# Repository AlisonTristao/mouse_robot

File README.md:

# mouse_robot
Projeto da PCB de um robo para simular uma rede neural baseada no estudo do comportamento de roedores utilizando Arduino Mega

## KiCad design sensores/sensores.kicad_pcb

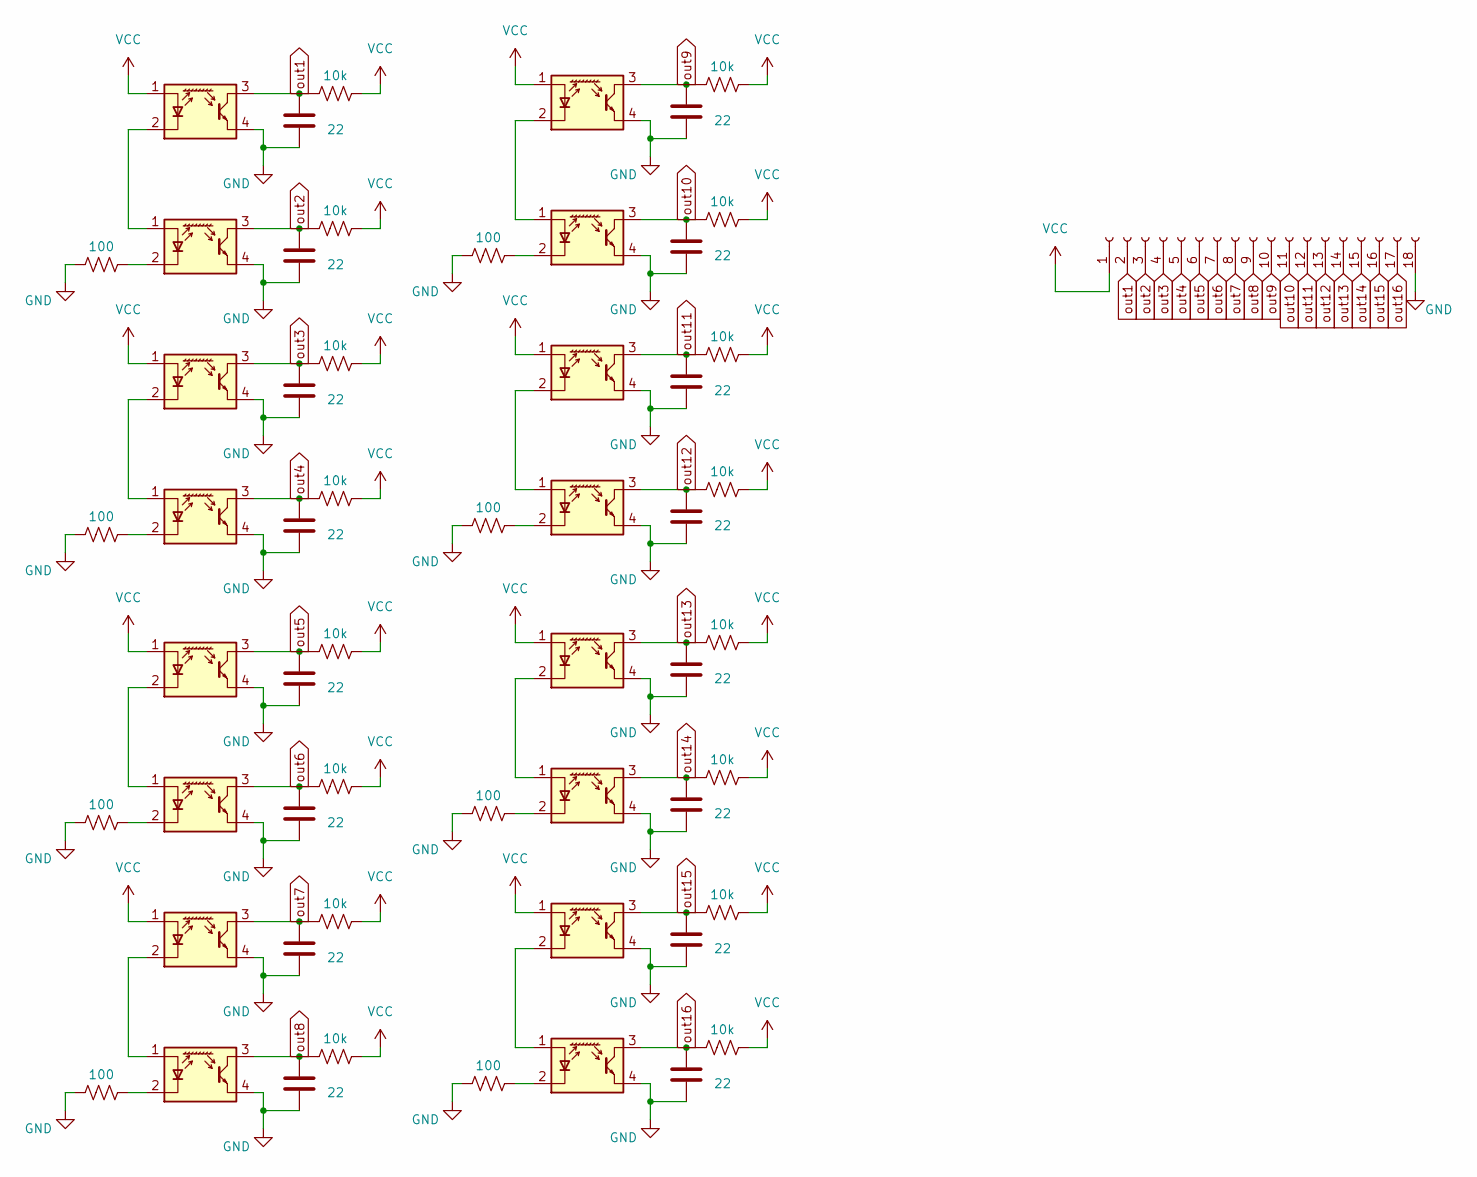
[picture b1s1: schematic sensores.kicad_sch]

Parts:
C1, C2, C3, C4, C5, C6, C7, C8, C9, C10, C11, C12, C13, C14, C15, C16: 22; C_1206_3216Metric
J1: Conn_01x18_Socket; PinSocket_1x18_P1.00mm_Vertical
R1, R4, R7, R8, R13, R14, R15, R16: 100; R_1206_3216Metric
R2, R3, R5, R6, R9, R10, R11, R12, R17, R18, R19, R20, R21, R22, R23, R24: 10k; R_1206_3216Metric
U1, U2, U3, U4, U5, U6, U7, U8, U9, U10, U11, U12, U13, U14, U15, U16: QRE1113GR; OnSemi_CASE100CY

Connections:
GND: C1.2, C2.2, C3.2, C4.2, C5.2, C6.2, C7.2, C8.2, C9.2, C10.2, C11.2, C12.2, C13.2, C14.2, C15.2, C16.2, J1.18, R1.1, R4.1, R7.1, R8.1, R13.1, R14.1, R15.1, R16.1, U1.4, U2.4, U3.4, U4.4, U5.4, U6.4, U7.4, U8.4, U9.4, U10.4, U11.4, U12.4, U13.4, U14.4, U15.4, U16.4
unnamed: U1.2 (K), U2.1 (A)
unnamed: R1.2, U2.2 (K)
unnamed: U3.2 (K), U4.1 (A)
unnamed: R4.2, U4.2 (K)
unnamed: U5.2 (K), U6.1 (A)
unnamed: R7.2, U6.2 (K)
unnamed: U7.2 (K), U8.1 (A)
unnamed: R8.2, U8.2 (K)
unnamed: U9.2 (K), U10.1 (A)
unnamed: R13.2, U10.2 (K)
unnamed: U11.2 (K), U12.1 (A)
unnamed: R14.2, U12.2 (K)
unnamed: U13.2 (K), U14.1 (A)
unnamed: R15.2, U14.2 (K)
unnamed: U15.2 (K), U16.1 (A)
unnamed: R16.2, U16.2 (K)
VCC: J1.1, R2.2, R3.2, R5.2, R6.2, R9.2, R10.2, R11.2, R12.2, R17.2, R18.2, R19.2, R20.2, R21.2, R22.2, R23.2, R24.2, U1.1 (A), U3.1 (A), U5.1 (A), U7.1 (A), U9.1 (A), U11.1 (A), U13.1 (A), U15.1 (A)
out1: C1.1, J1.2, R3.1, U1.3
out2: C2.1, J1.3, R2.1, U2.3
out3: C3.1, J1.4, R5.1, U3.3
out4: C4.1, J1.5, R6.1, U4.3
out5: C5.1, J1.6, R9.1, U5.3
out6: C6.1, J1.7, R10.1, U6.3
out7: C7.1, J1.8, R11.1, U7.3
out8: C8.1, J1.9, R12.1, U8.3
out9: C9.1, J1.10, R17.1, U9.3
out10: C10.1, J1.11, R18.1, U10.3
out11: C11.1, J1.12, R19.1, U11.3
out12: C12.1, J1.13, R20.1, U12.3
out13: C13.1, J1.14, R21.1, U13.3
out14: C14.1, J1.15, R22.1, U14.3
out15: C15.1, J1.16, R23.1, U15.3
out16: C16.1, J1.17, R24.1, U16.3

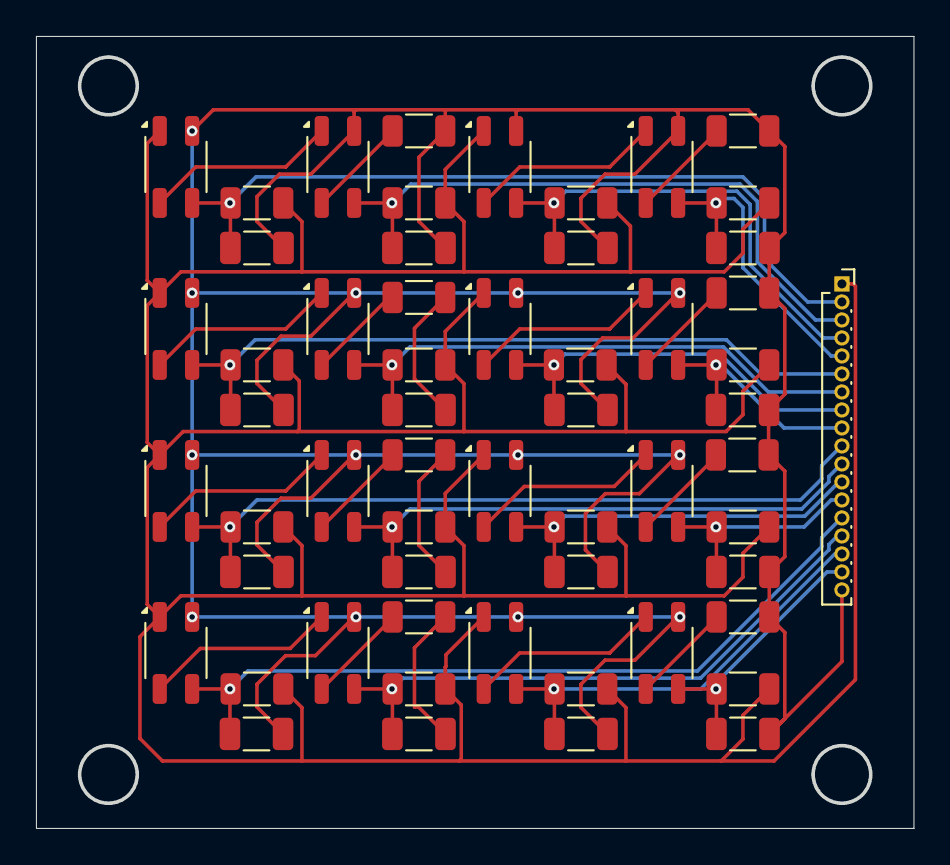
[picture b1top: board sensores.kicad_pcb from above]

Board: 2 copper layers, 48.6 x 43.9 mm, 57 parts (0 on the bottom side), 34 nets.

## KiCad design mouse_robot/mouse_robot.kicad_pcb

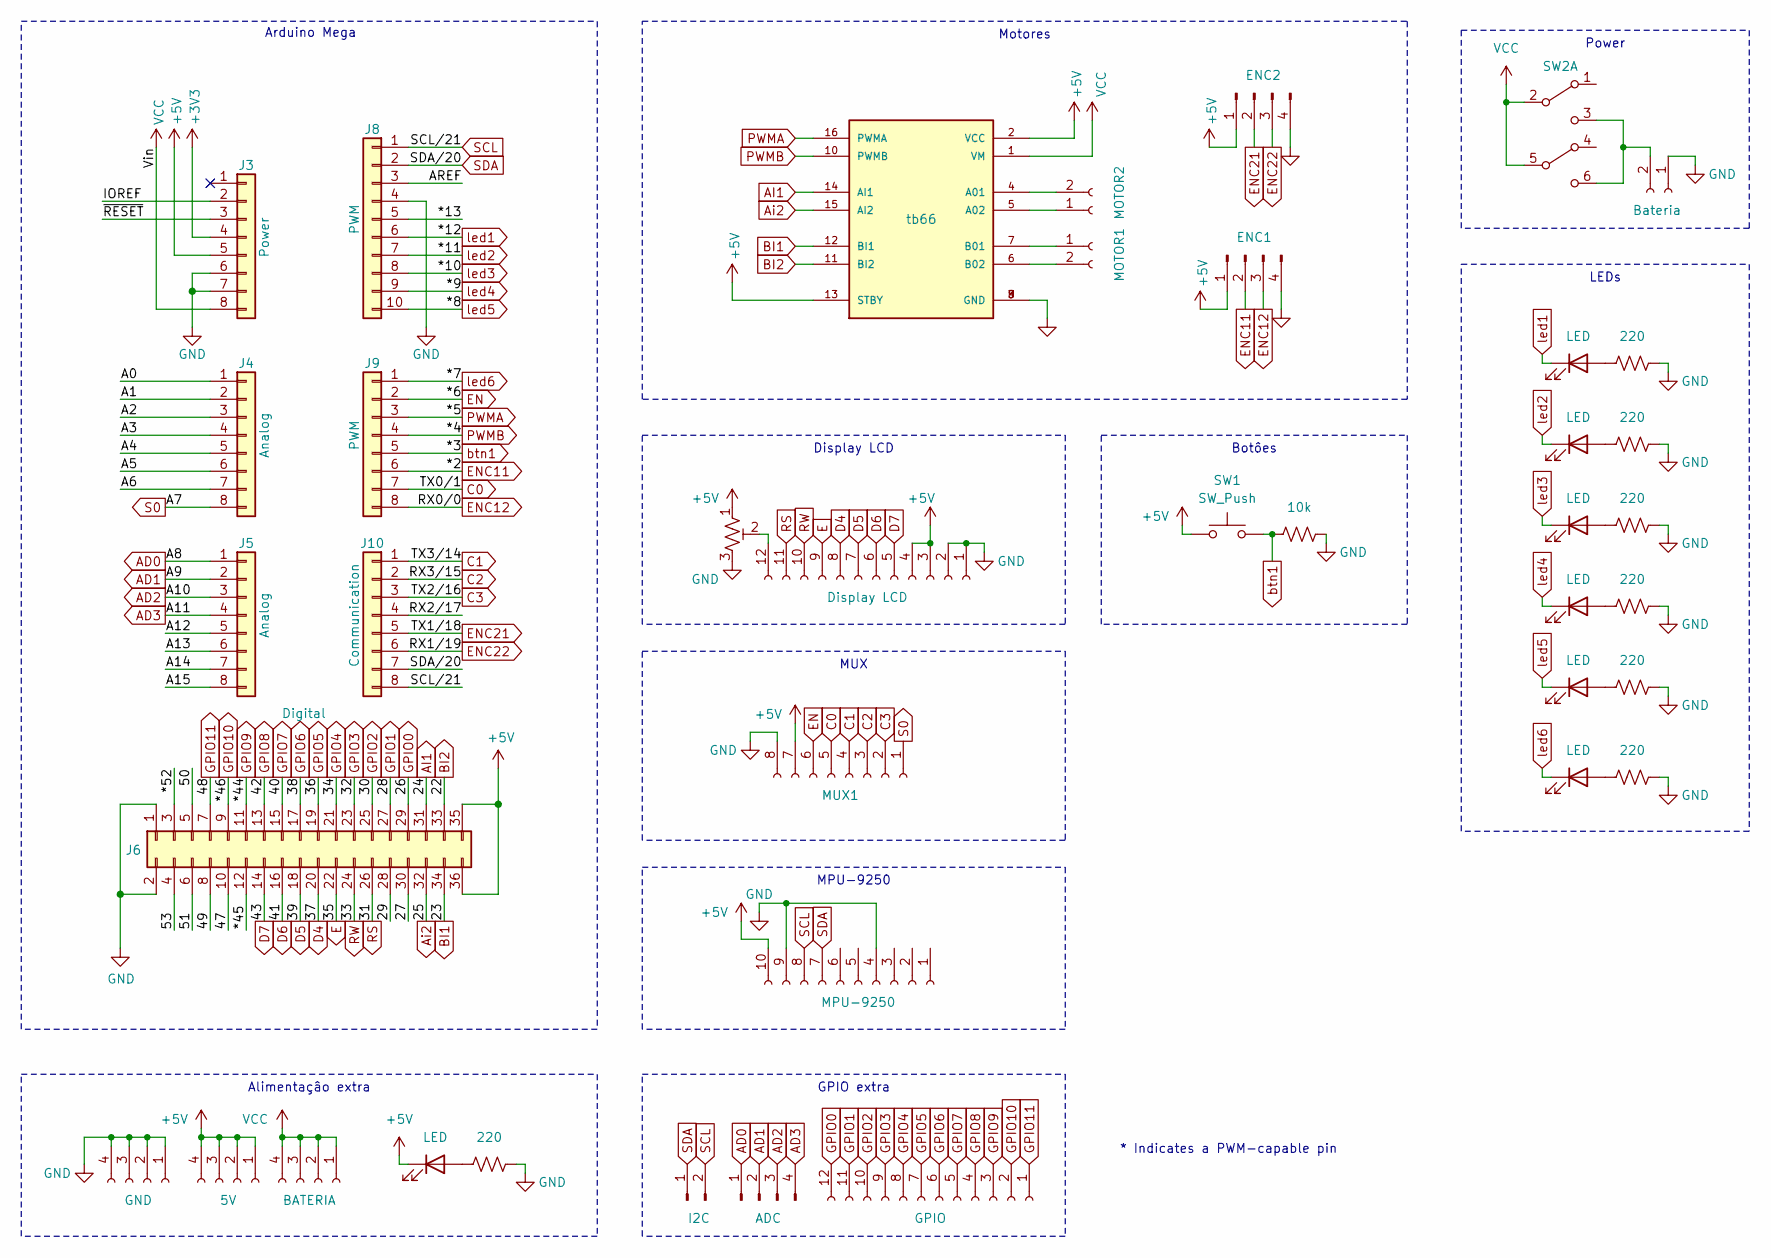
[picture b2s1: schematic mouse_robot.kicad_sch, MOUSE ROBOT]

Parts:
D1, D2, D3, D4, D5, D6, D7: LED; LED_1206_3216Metric
J1: GND; Molex_KK-254_AE-6410-04A_1x04_P2.54mm_Vertical
J2: 5V; Molex_KK-254_AE-6410-04A_1x04_P2.54mm_Vertical
J3: Power; PinSocket_1x08_P2.54mm_Vertical
J4, J5: Analog; PinSocket_1x08_P2.54mm_Vertical
J6: Digital; PinSocket_2x18_P2.54mm_Vertical
J7: BATERIA; Molex_KK-254_AE-6410-04A_1x04_P2.54mm_Vertical
J8: PWM; PinSocket_1x10_P2.54mm_Vertical
J9: PWM; PinSocket_1x08_P2.54mm_Vertical
J10: Communication; PinSocket_1x08_P2.54mm_Vertical
J11: I2C; Molex_KK-254_AE-6410-02A_1x02_P2.54mm_Vertical
J12: ADC; Molex_KK-254_AE-6410-04A_1x04_P2.54mm_Vertical
J13: MPU-9250; Molex_KK-254_AE-6410-10A_1x10_P2.54mm_Vertical
J14: Display LCD; Molex_KK-254_AE-6410-12A_1x12_P2.54mm_Vertical
J15: GPIO; Molex_KK-254_AE-6410-12A_1x12_P2.54mm_Vertical
MUX1: Conn_01x08_Socket; Molex_KK-254_AE-6410-08A_1x08_P2.54mm_Vertical
R1, R3, R4, R5, R6, R7, R8: 220; R_1206_3216Metric
R2: 10k; R_1206_3216Metric
RV1: Potenciometro; Potentiometer_Vishay_T73YP_Vertical
SW1: SW_Push; SW_PUSH_6mm_H4.3mm
SW2: SW_DPDT_x2
U1: tb66; MODULE_ROB-14450; PARTREV 11-13-17
con1: MOTOR2; Molex_KK-254_AE-6410-02A_1x02_P2.54mm_Vertical
con2: MOTOR1; Molex_KK-254_AE-6410-02A_1x02_P2.54mm_Vertical
con3: ENC1; Molex_KK-254_AE-6410-04A_1x04_P2.54mm_Vertical
con4: ENC2; Molex_KK-254_AE-6410-04A_1x04_P2.54mm_Vertical
con5: Bateria; Molex_KK-254_AE-6410-02A_1x02_P2.54mm_Vertical

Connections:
+3V3: J3.4
+5V: D1.1 (K), J2.1, J2.2, J2.3, J2.4, J3.5, J6.35, J6.36, J13.10, J14.3, J14.4, MUX1.7, RV1.1, SW1.1, U1.2 (VCC), U1.13 (STBY), con3.1, con4.1; also elsewhere on the board
/27: J6.30
/29: J6.28
/47: J6.10
/49: J6.8
/50: J6.5
/51: J6.6
/53: J6.4
/*13: J8.5
/*45: J6.12
/*52: J6.3
/A0: J4.1
/A1: J4.2
/A2: J4.3
/A3: J4.4
/A4: J4.5
/A5: J4.6
/A6: J4.7
/A12: J5.5
/A13: J5.6
/A14: J5.7
/A15: J5.8
/AREF: J8.3
/IOREF: J3.2
/RX2/17: J10.4
/~RESET: J3.3
AD0: J5.1, J12.1
AD1: J5.2, J12.2
AD2: J5.3, J12.3
AD3: J5.4, J12.4
AI1: J6.31, U1.14 (AI1)
Ai2: J6.32, U1.15 (AI2)
BI1: J6.34, U1.12 (BI1)
BI2: J6.33, U1.11 (BI2)
C0: J9.7, MUX1.5; also elsewhere on the board
C1: J10.1, MUX1.4; also elsewhere on the board
C2: J10.2, MUX1.3; also elsewhere on the board
C3: J10.3, MUX1.2; also elsewhere on the board
D4: J6.20, J14.8
D5: J6.18, J14.7
D6: J6.16, J14.6
D7: J6.14, J14.5
E: J6.22, J14.9
EN: J9.2, MUX1.6; also elsewhere on the board
ENC11: J9.6, con3.2
ENC12: J9.8, con3.3
ENC21: J10.5, con4.2
ENC22: J10.6, con4.3
GND: J1.1, J1.2, J1.3, J1.4, J3.6, J3.7, J6.1, J6.2, J8.4, J13.4, J13.9, J14.1, J14.2, MUX1.8, R1.1, R2.1, R3.1, R4.1, R5.1, R6.1, R7.1, R8.1, RV1.3, U1.3 (GND), U1.8 (GND), U1.9 (GND), con3.4, con4.4, con5.1; also elsewhere on the board
GPIO0: J6.29, J15.12
GPIO1: J6.27, J15.11
GPIO2: J6.25, J15.10
GPIO3: J6.23, J15.9
GPIO4: J6.21, J15.8
GPIO5: J6.19, J15.7
GPIO6: J6.17, J15.6
GPIO7: J6.15, J15.5
GPIO8: J6.13, J15.4
GPIO9: J6.11, J15.3
GPIO10: J6.9, J15.2
GPIO11: J6.7, J15.1
unnamed: D1.2 (A), R1.2
unnamed: D2.2 (A), R3.2
unnamed: D3.2 (A), R4.2
unnamed: D4.2 (A), R5.2
unnamed: D5.2 (A), R6.2
unnamed: D6.2 (A), R7.2
unnamed: D7.2 (A), R8.2
unnamed: J14.12, RV1.2
unnamed: SW2.3 (C), SW2.6 (C), con5.2
unnamed: U1.4 (A01), con1.2
unnamed: U1.5 (A02), con1.1
unnamed: U1.7 (B01), con2.1
unnamed: U1.6 (B02), con2.2
PWMA: J9.3, U1.16 (PWMA)
PWMB: J9.4, U1.10 (PWMB)
RS: J6.26, J14.11
RW: J6.24, J14.10
S0: J4.8, MUX1.1; also elsewhere on the board
SCL: J8.1, J10.8, J11.2, J13.8
SDA: J8.2, J10.7, J11.1, J13.7
VCC: J3.8, J7.1, J7.2, J7.3, J7.4, SW2.2 (B), SW2.5 (B), U1.1 (VM)
btn1: J9.5, R2.2, SW1.2
led1: D2.1 (K), J8.6
led2: D3.1 (K), J8.7
led3: D4.1 (K), J8.8
led4: D5.1 (K), J8.9
led5: D6.1 (K), J8.10
led6: D7.1 (K), J9.1

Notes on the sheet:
MUX
Display LCD
GPIO extra
MPU-9250
Botôes
Alimentaçâo extra
Power
LEDs
Motores
Arduino Mega
* Indicates a PWM-capable pin

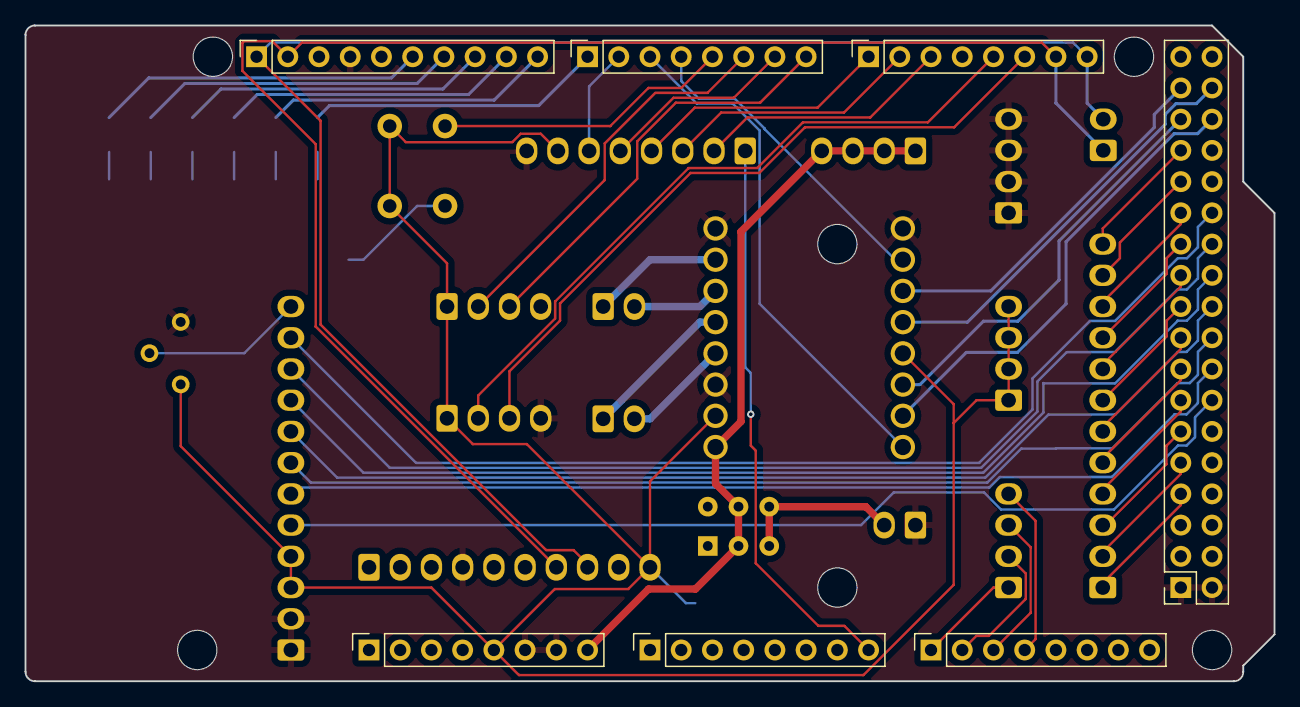
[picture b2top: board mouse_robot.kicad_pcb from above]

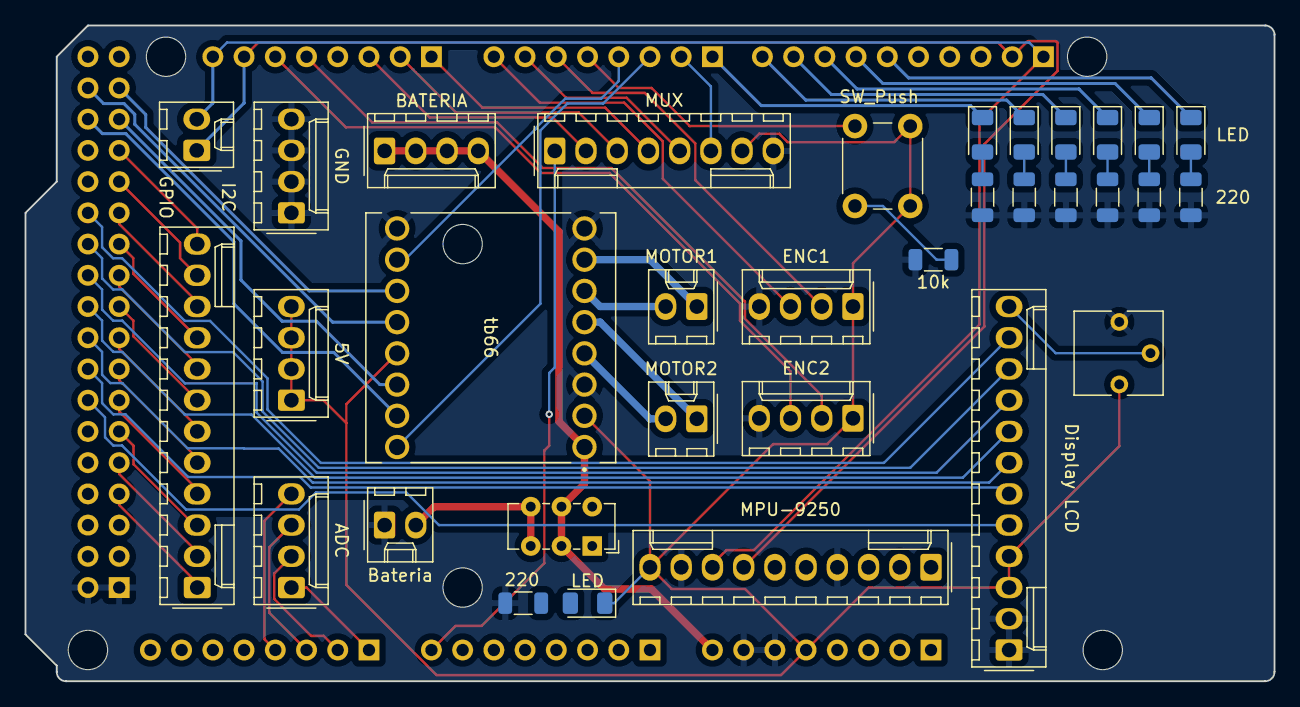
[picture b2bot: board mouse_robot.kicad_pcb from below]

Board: 2 copper layers, 101.6 x 53.3 mm, 46 parts (33 on the bottom side), 64 nets.

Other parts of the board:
MH1, MH2, MH3, MH4, MH5, MH6: MountingHole_3.2mm
MUX: Conn_01x08_Socket; Molex_KK-254_AE-6410-08A_1x08_P2.54mm_Vertical

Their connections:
+5V: MUX.7; also elsewhere on the board
C0: MUX.5; also elsewhere on the board
C1: MUX.4; also elsewhere on the board
C2: MUX.3; also elsewhere on the board
C3: MUX.2; also elsewhere on the board
EN: MUX.6; also elsewhere on the board
GND: MUX.8; also elsewhere on the board
S0: MUX.1; also elsewhere on the board

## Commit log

2024-06-17 init project
2024-06-18 primeira ideia pronta
2024-06-22 eletric scheme ok
2024-07-26 componentes ok
2024-08-16 roteamento init
2024-08-16 pronto
2024-08-16 sensores prontos
